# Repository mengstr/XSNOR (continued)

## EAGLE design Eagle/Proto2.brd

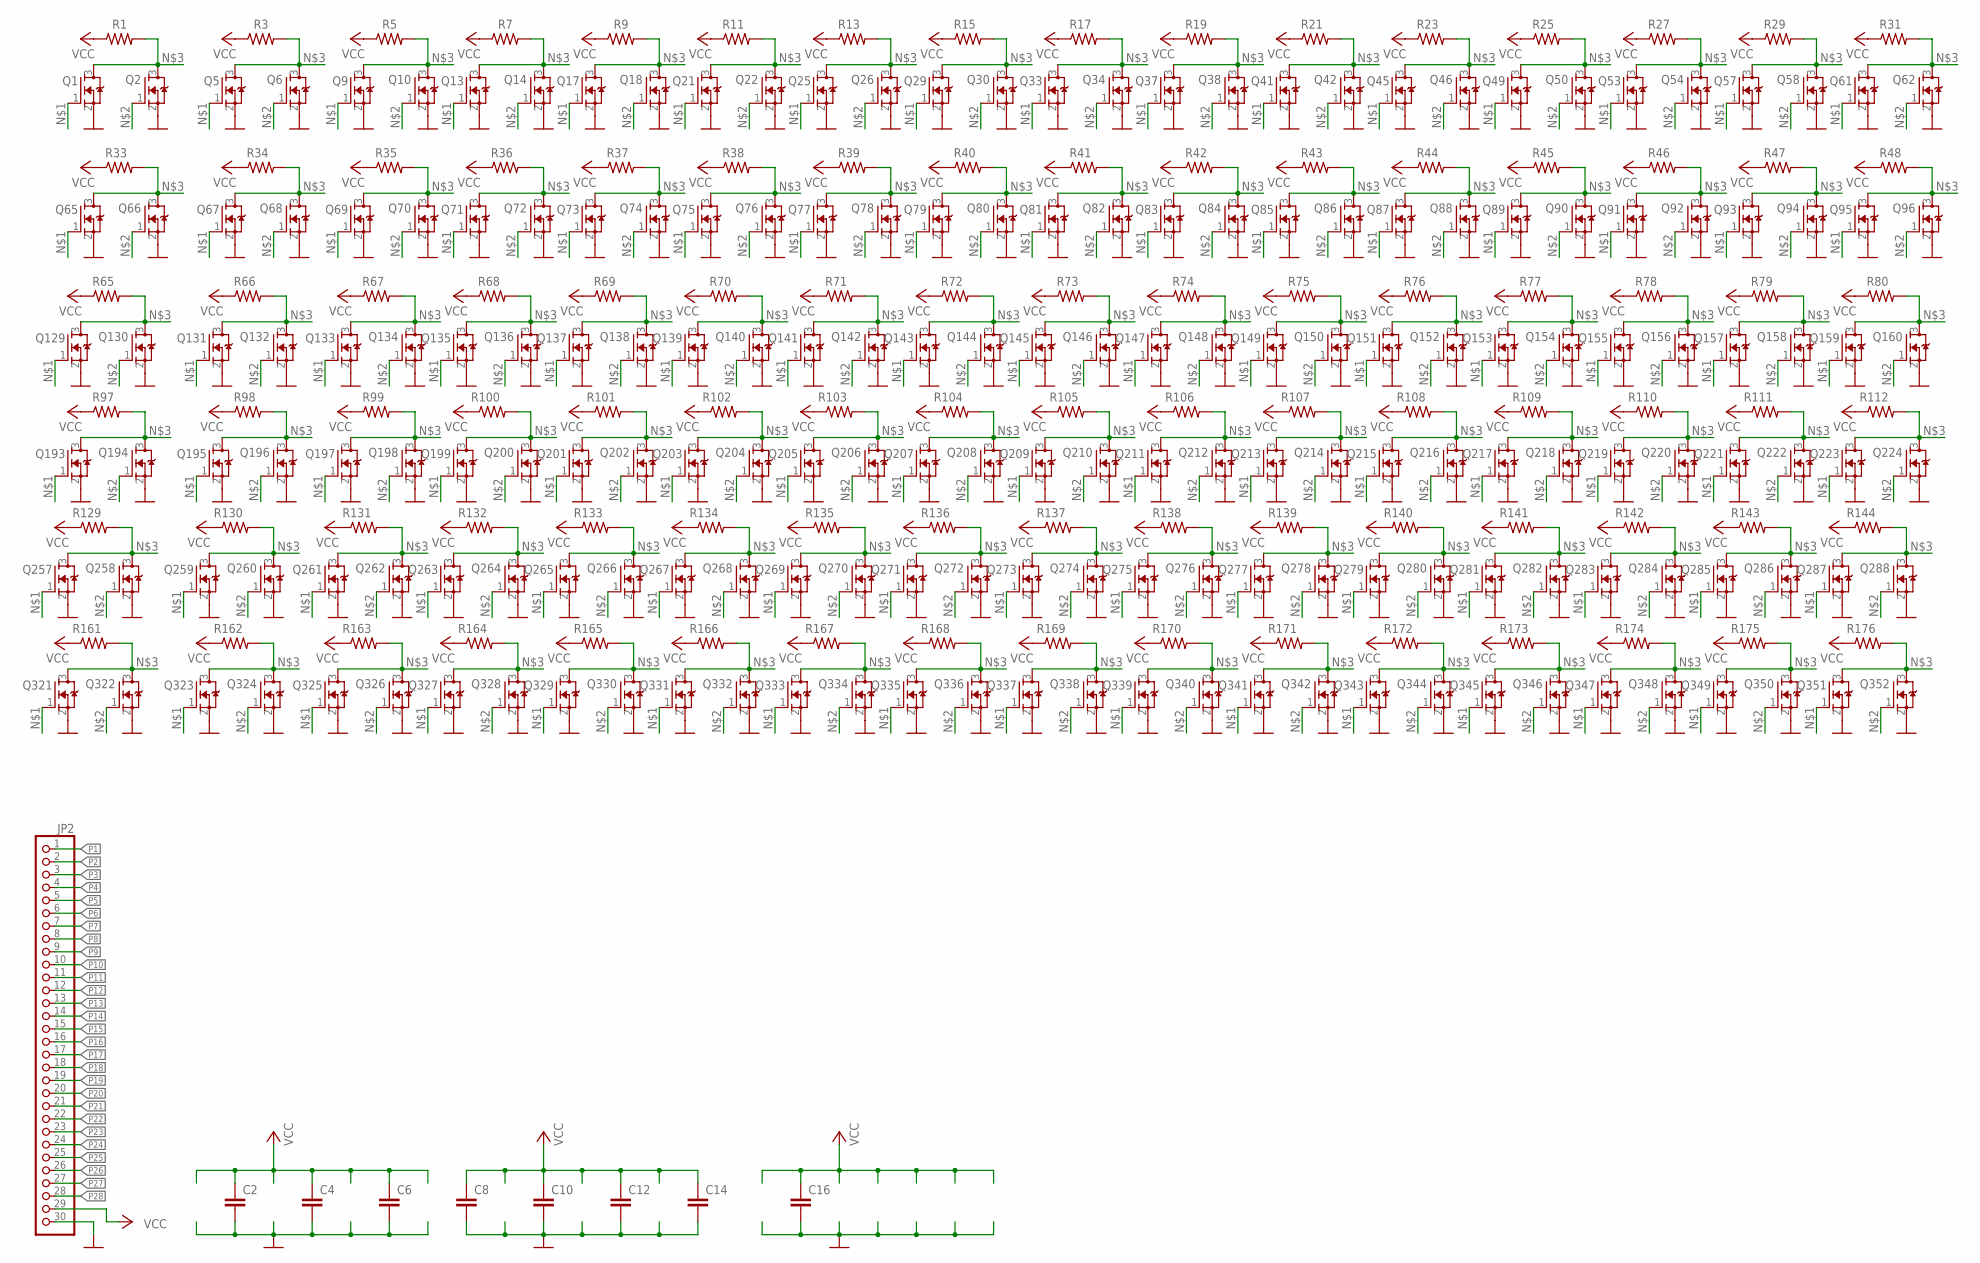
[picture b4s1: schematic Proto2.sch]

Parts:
C2, C4, C6, C8, C10, C12, C14, C16: C-EUC0805K; C0805K
JP2: PINHD-1X30; 1X30
Q1, Q2, Q5, Q6, Q9, Q10, Q13, Q14, Q17, Q18, Q21, Q22, Q25, Q26, Q29, Q30, Q33, Q34, Q37, Q38, Q41, Q42, Q45, Q46, Q49, Q50, Q53, Q54, Q57, Q58, Q61, Q62, Q65, Q66, Q67, Q68, Q69, Q70, Q71, Q72, Q73, Q74, Q75, Q76, Q77, Q78, Q79, Q80, Q81, Q82, Q83, Q84, Q85, Q86, Q87, Q88, Q89, Q90, Q91, Q92, Q93, Q94, Q95, Q96, Q129, Q130, Q131, Q132, Q133, Q134, Q135, Q136, Q137, Q138, Q139, Q140, Q141, Q142, Q143, Q144, Q145, Q146, Q147, Q148, Q149, Q150, Q151, Q152, Q153, Q154, Q155, Q156, Q157, Q158, Q159, Q160, Q193, Q194, Q195, Q196, Q197, Q198, Q199, Q200, Q201, Q202, Q203, Q204, Q205, Q206, Q207, Q208, Q209, Q210, Q211, Q212, Q213, Q214, Q215, Q216, Q217, Q218, Q219, Q220, Q221, Q222, Q223, Q224, Q257, Q258, Q259, Q260, Q261, Q262, Q263, Q264, Q265, Q266, Q267, Q268, Q269, Q270, Q271, Q272, Q273, Q274, Q275, Q276, Q277, Q278, Q279, Q280, Q281, Q282, Q283, Q284, Q285, Q286, Q287, Q288, Q321, Q322, Q323, Q324, Q325, Q326, Q327, Q328, Q329, Q330, Q331, Q332, Q333, Q334, Q335, Q336, Q337, Q338, Q339, Q340, Q341, Q342, Q343, Q344, Q345, Q346, Q347, Q348, Q349, Q350, Q351, Q352: 310mA/60V/1.6Ω; SOT23
R1, R3, R5, R7, R9, R11, R13, R15, R17, R19, R21, R23, R25, R27, R29, R31, R33, R34, R35, R36, R37, R38, R39, R40, R41, R42, R43, R44, R45, R46, R47, R48, R65, R66, R67, R68, R69, R70, R71, R72, R73, R74, R75, R76, R77, R78, R79, R80, R97, R98, R99, R100, R101, R102, R103, R104, R105, R106, R107, R108, R109, R110, R111, R112, R129, R130, R131, R132, R133, R134, R135, R136, R137, R138, R139, R140, R141, R142, R143, R144, R161, R162, R163, R164, R165, R166, R167, R168, R169, R170, R171, R172, R173, R174, R175, R176: 0805

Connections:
GND: C2.2, C4.2, C6.2, C8.2, C10.2, C12.2, C14.2, C16.2, JP2.30, Q1.2 (S), Q2.2 (S), Q5.2 (S), Q6.2 (S), Q9.2 (S), Q10.2 (S), Q13.2 (S), Q14.2 (S), Q17.2 (S), Q18.2 (S), Q21.2 (S), Q22.2 (S), Q25.2 (S), Q26.2 (S), Q29.2 (S), Q30.2 (S), Q33.2 (S), Q34.2 (S), Q37.2 (S), Q38.2 (S), Q41.2 (S), Q42.2 (S), Q45.2 (S), Q46.2 (S), Q49.2 (S), Q50.2 (S), Q53.2 (S), Q54.2 (S), Q57.2 (S), Q58.2 (S), Q61.2 (S), Q62.2 (S), Q65.2 (S), Q66.2 (S), Q67.2 (S), Q68.2 (S), Q69.2 (S), Q70.2 (S), Q71.2 (S), Q72.2 (S), Q73.2 (S), Q74.2 (S), Q75.2 (S), Q76.2 (S), Q77.2 (S), Q78.2 (S), Q79.2 (S), Q80.2 (S), Q81.2 (S), Q82.2 (S), Q83.2 (S), Q84.2 (S), Q85.2 (S), Q86.2 (S), Q87.2 (S), Q88.2 (S), Q89.2 (S), Q90.2 (S), Q91.2 (S), Q92.2 (S), Q93.2 (S), Q94.2 (S), Q95.2 (S), Q96.2 (S), Q129.2 (S), Q130.2 (S), Q131.2 (S), Q132.2 (S), Q133.2 (S), Q134.2 (S), Q135.2 (S), Q136.2 (S), Q137.2 (S), Q138.2 (S), Q139.2 (S), Q140.2 (S), Q141.2 (S), Q142.2 (S), Q143.2 (S), Q144.2 (S), Q145.2 (S), Q146.2 (S), Q147.2 (S), Q148.2 (S), Q149.2 (S), Q150.2 (S), Q151.2 (S), Q152.2 (S), Q153.2 (S), Q154.2 (S), Q155.2 (S), Q156.2 (S), Q157.2 (S), Q158.2 (S), Q159.2 (S), Q160.2 (S), Q193.2 (S), Q194.2 (S), Q195.2 (S), Q196.2 (S), Q197.2 (S), Q198.2 (S), Q199.2 (S), Q200.2 (S), Q201.2 (S), Q202.2 (S), Q203.2 (S), Q204.2 (S), Q205.2 (S), Q206.2 (S), Q207.2 (S), Q208.2 (S), Q209.2 (S), Q210.2 (S), Q211.2 (S), Q212.2 (S), Q213.2 (S), Q214.2 (S), Q215.2 (S), Q216.2 (S), Q217.2 (S), Q218.2 (S), Q219.2 (S), Q220.2 (S), Q221.2 (S), Q222.2 (S), Q223.2 (S), Q224.2 (S), Q257.2 (S), Q258.2 (S), Q259.2 (S), Q260.2 (S), Q261.2 (S), Q262.2 (S), Q263.2 (S), Q264.2 (S), Q265.2 (S), Q266.2 (S), Q267.2 (S), Q268.2 (S), Q269.2 (S), Q270.2 (S), Q271.2 (S), Q272.2 (S), Q273.2 (S), Q274.2 (S), Q275.2 (S), Q276.2 (S), Q277.2 (S), Q278.2 (S), Q279.2 (S), Q280.2 (S), Q281.2 (S), Q282.2 (S), Q283.2 (S), Q284.2 (S), Q285.2 (S), Q286.2 (S), Q287.2 (S), Q288.2 (S), Q321.2 (S), Q322.2 (S), Q323.2 (S), Q324.2 (S), Q325.2 (S), Q326.2 (S), Q327.2 (S), Q328.2 (S), Q329.2 (S), Q330.2 (S), Q331.2 (S), Q332.2 (S), Q333.2 (S), Q334.2 (S), Q335.2 (S), Q336.2 (S), Q337.2 (S), Q338.2 (S), Q339.2 (S), Q340.2 (S), Q341.2 (S), Q342.2 (S), Q343.2 (S), Q344.2 (S), Q345.2 (S), Q346.2 (S), Q347.2 (S), Q348.2 (S), Q349.2 (S), Q350.2 (S), Q351.2 (S), Q352.2 (S)
unnamed: Q1.1 (G), Q5.1 (G), Q9.1 (G), Q13.1 (G), Q17.1 (G), Q21.1 (G), Q25.1 (G), Q29.1 (G), Q33.1 (G), Q37.1 (G), Q41.1 (G), Q45.1 (G), Q49.1 (G), Q53.1 (G), Q57.1 (G), Q61.1 (G), Q65.1 (G), Q67.1 (G), Q69.1 (G), Q71.1 (G), Q73.1 (G), Q75.1 (G), Q77.1 (G), Q79.1 (G), Q81.1 (G), Q83.1 (G), Q85.1 (G), Q87.1 (G), Q89.1 (G), Q91.1 (G), Q93.1 (G), Q95.1 (G), Q129.1 (G), Q131.1 (G), Q133.1 (G), Q135.1 (G), Q137.1 (G), Q139.1 (G), Q141.1 (G), Q143.1 (G), Q145.1 (G), Q147.1 (G), Q149.1 (G), Q151.1 (G), Q153.1 (G), Q155.1 (G), Q157.1 (G), Q159.1 (G), Q193.1 (G), Q195.1 (G), Q197.1 (G), Q199.1 (G), Q201.1 (G), Q203.1 (G), Q205.1 (G), Q207.1 (G), Q209.1 (G), Q211.1 (G), Q213.1 (G), Q215.1 (G), Q217.1 (G), Q219.1 (G), Q221.1 (G), Q223.1 (G), Q257.1 (G), Q259.1 (G), Q261.1 (G), Q263.1 (G), Q265.1 (G), Q267.1 (G), Q269.1 (G), Q271.1 (G), Q273.1 (G), Q275.1 (G), Q277.1 (G), Q279.1 (G), Q281.1 (G), Q283.1 (G), Q285.1 (G), Q287.1 (G), Q321.1 (G), Q323.1 (G), Q325.1 (G), Q327.1 (G), Q329.1 (G), Q331.1 (G), Q333.1 (G), Q335.1 (G), Q337.1 (G), Q339.1 (G), Q341.1 (G), Q343.1 (G), Q345.1 (G), Q347.1 (G), Q349.1 (G), Q351.1 (G)
unnamed: Q2.1 (G), Q6.1 (G), Q10.1 (G), Q14.1 (G), Q18.1 (G), Q22.1 (G), Q26.1 (G), Q30.1 (G), Q34.1 (G), Q38.1 (G), Q42.1 (G), Q46.1 (G), Q50.1 (G), Q54.1 (G), Q58.1 (G), Q62.1 (G), Q66.1 (G), Q68.1 (G), Q70.1 (G), Q72.1 (G), Q74.1 (G), Q76.1 (G), Q78.1 (G), Q80.1 (G), Q82.1 (G), Q84.1 (G), Q86.1 (G), Q88.1 (G), Q90.1 (G), Q92.1 (G), Q94.1 (G), Q96.1 (G), Q130.1 (G), Q132.1 (G), Q134.1 (G), Q136.1 (G), Q138.1 (G), Q140.1 (G), Q142.1 (G), Q144.1 (G), Q146.1 (G), Q148.1 (G), Q150.1 (G), Q152.1 (G), Q154.1 (G), Q156.1 (G), Q158.1 (G), Q160.1 (G), Q194.1 (G), Q196.1 (G), Q198.1 (G), Q200.1 (G), Q202.1 (G), Q204.1 (G), Q206.1 (G), Q208.1 (G), Q210.1 (G), Q212.1 (G), Q214.1 (G), Q216.1 (G), Q218.1 (G), Q220.1 (G), Q222.1 (G), Q224.1 (G), Q258.1 (G), Q260.1 (G), Q262.1 (G), Q264.1 (G), Q266.1 (G), Q268.1 (G), Q270.1 (G), Q272.1 (G), Q274.1 (G), Q276.1 (G), Q278.1 (G), Q280.1 (G), Q282.1 (G), Q284.1 (G), Q286.1 (G), Q288.1 (G), Q322.1 (G), Q324.1 (G), Q326.1 (G), Q328.1 (G), Q330.1 (G), Q332.1 (G), Q334.1 (G), Q336.1 (G), Q338.1 (G), Q340.1 (G), Q342.1 (G), Q344.1 (G), Q346.1 (G), Q348.1 (G), Q350.1 (G), Q352.1 (G)
unnamed: Q1.3 (D), Q2.3 (D), Q5.3 (D), Q6.3 (D), Q9.3 (D), Q10.3 (D), Q13.3 (D), Q14.3 (D), Q17.3 (D), Q18.3 (D), Q21.3 (D), Q22.3 (D), Q25.3 (D), Q26.3 (D), Q29.3 (D), Q30.3 (D), Q33.3 (D), Q34.3 (D), Q37.3 (D), Q38.3 (D), Q41.3 (D), Q42.3 (D), Q45.3 (D), Q46.3 (D), Q49.3 (D), Q50.3 (D), Q53.3 (D), Q54.3 (D), Q57.3 (D), Q58.3 (D), Q61.3 (D), Q62.3 (D), Q65.3 (D), Q66.3 (D), Q67.3 (D), Q68.3 (D), Q69.3 (D), Q70.3 (D), Q71.3 (D), Q72.3 (D), Q73.3 (D), Q74.3 (D), Q75.3 (D), Q76.3 (D), Q77.3 (D), Q78.3 (D), Q79.3 (D), Q80.3 (D), Q81.3 (D), Q82.3 (D), Q83.3 (D), Q84.3 (D), Q85.3 (D), Q86.3 (D), Q87.3 (D), Q88.3 (D), Q89.3 (D), Q90.3 (D), Q91.3 (D), Q92.3 (D), Q93.3 (D), Q94.3 (D), Q95.3 (D), Q96.3 (D), Q129.3 (D), Q130.3 (D), Q131.3 (D), Q132.3 (D), Q133.3 (D), Q134.3 (D), Q135.3 (D), Q136.3 (D), Q137.3 (D), Q138.3 (D), Q139.3 (D), Q140.3 (D), Q141.3 (D), Q142.3 (D), Q143.3 (D), Q144.3 (D), Q145.3 (D), Q146.3 (D), Q147.3 (D), Q148.3 (D), Q149.3 (D), Q150.3 (D), Q151.3 (D), Q152.3 (D), Q153.3 (D), Q154.3 (D), Q155.3 (D), Q156.3 (D), Q157.3 (D), Q158.3 (D), Q159.3 (D), Q160.3 (D), Q193.3 (D), Q194.3 (D), Q195.3 (D), Q196.3 (D), Q197.3 (D), Q198.3 (D), Q199.3 (D), Q200.3 (D), Q201.3 (D), Q202.3 (D), Q203.3 (D), Q204.3 (D), Q205.3 (D), Q206.3 (D), Q207.3 (D), Q208.3 (D), Q209.3 (D), Q210.3 (D), Q211.3 (D), Q212.3 (D), Q213.3 (D), Q214.3 (D), Q215.3 (D), Q216.3 (D), Q217.3 (D), Q218.3 (D), Q219.3 (D), Q220.3 (D), Q221.3 (D), Q222.3 (D), Q223.3 (D), Q224.3 (D), Q257.3 (D), Q258.3 (D), Q259.3 (D), Q260.3 (D), Q261.3 (D), Q262.3 (D), Q263.3 (D), Q264.3 (D), Q265.3 (D), Q266.3 (D), Q267.3 (D), Q268.3 (D), Q269.3 (D), Q270.3 (D), Q271.3 (D), Q272.3 (D), Q273.3 (D), Q274.3 (D), Q275.3 (D), Q276.3 (D), Q277.3 (D), Q278.3 (D), Q279.3 (D), Q280.3 (D), Q281.3 (D), Q282.3 (D), Q283.3 (D), Q284.3 (D), Q285.3 (D), Q286.3 (D), Q287.3 (D), Q288.3 (D), Q321.3 (D), Q322.3 (D), Q323.3 (D), Q324.3 (D), Q325.3 (D), Q326.3 (D), Q327.3 (D), Q328.3 (D), Q329.3 (D), Q330.3 (D), Q331.3 (D), Q332.3 (D), Q333.3 (D), Q334.3 (D), Q335.3 (D), Q336.3 (D), Q337.3 (D), Q338.3 (D), Q339.3 (D), Q340.3 (D), Q341.3 (D), Q342.3 (D), Q343.3 (D), Q344.3 (D), Q345.3 (D), Q346.3 (D), Q347.3 (D), Q348.3 (D), Q349.3 (D), Q350.3 (D), Q351.3 (D), Q352.3 (D), R1.2, R3.2, R5.2, R7.2, R9.2, R11.2, R13.2, R15.2, R17.2, R19.2, R21.2, R23.2, R25.2, R27.2, R29.2, R31.2, R33.2, R34.2, R35.2, R36.2, R37.2, R38.2, R39.2, R40.2, R41.2, R42.2, R43.2, R44.2, R45.2, R46.2, R47.2, R48.2, R65.2, R66.2, R67.2, R68.2, R69.2, R70.2, R71.2, R72.2, R73.2, R74.2, R75.2, R76.2, R77.2, R78.2, R79.2, R80.2, R97.2, R98.2, R99.2, R100.2, R101.2, R102.2, R103.2, R104.2, R105.2, R106.2, R107.2, R108.2, R109.2, R110.2, R111.2, R112.2, R129.2, R130.2, R131.2, R132.2, R133.2, R134.2, R135.2, R136.2, R137.2, R138.2, R139.2, R140.2, R141.2, R142.2, R143.2, R144.2, R161.2, R162.2, R163.2, R164.2, R165.2, R166.2, R167.2, R168.2, R169.2, R170.2, R171.2, R172.2, R173.2, R174.2, R175.2, R176.2
P1: JP2.1
P2: JP2.2
P3: JP2.3
P4: JP2.4
P5: JP2.5
P6: JP2.6
P7: JP2.7
P8: JP2.8
P9: JP2.9
P10: JP2.10
P11: JP2.11
P12: JP2.12
P13: JP2.13
P14: JP2.14
P15: JP2.15
P16: JP2.16
P17: JP2.17
P18: JP2.18
P19: JP2.19
P20: JP2.20
P21: JP2.21
P22: JP2.22
P23: JP2.23
P24: JP2.24
P25: JP2.25
P26: JP2.26
P27: JP2.27
P28: JP2.28
VCC: C2.1, C4.1, C6.1, C8.1, C10.1, C12.1, C14.1, C16.1, JP2.29, R1.1, R3.1, R5.1, R7.1, R9.1, R11.1, R13.1, R15.1, R17.1, R19.1, R21.1, R23.1, R25.1, R27.1, R29.1, R31.1, R33.1, R34.1, R35.1, R36.1, R37.1, R38.1, R39.1, R40.1, R41.1, R42.1, R43.1, R44.1, R45.1, R46.1, R47.1, R48.1, R65.1, R66.1, R67.1, R68.1, R69.1, R70.1, R71.1, R72.1, R73.1, R74.1, R75.1, R76.1, R77.1, R78.1, R79.1, R80.1, R97.1, R98.1, R99.1, R100.1, R101.1, R102.1, R103.1, R104.1, R105.1, R106.1, R107.1, R108.1, R109.1, R110.1, R111.1, R112.1, R129.1, R130.1, R131.1, R132.1, R133.1, R134.1, R135.1, R136.1, R137.1, R138.1, R139.1, R140.1, R141.1, R142.1, R143.1, R144.1, R161.1, R162.1, R163.1, R164.1, R165.1, R166.1, R167.1, R168.1, R169.1, R170.1, R171.1, R172.1, R173.1, R174.1, R175.1, R176.1

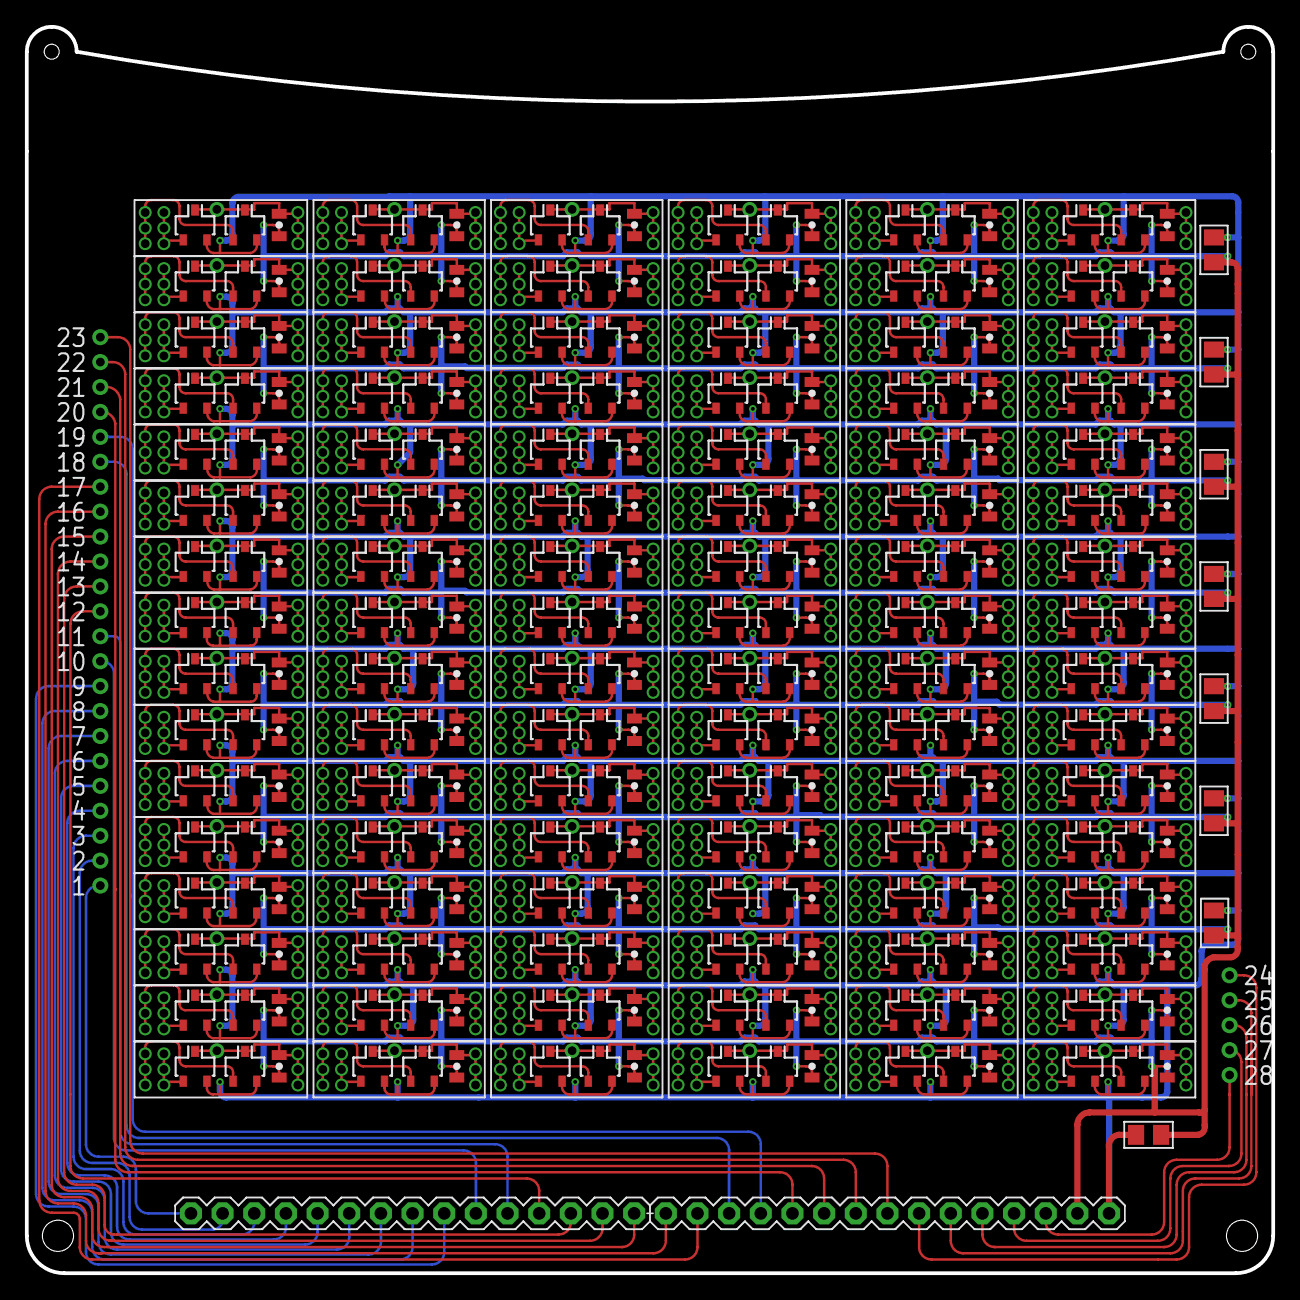
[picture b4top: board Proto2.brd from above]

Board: 2 copper layers, 100.0 x 100.0 mm, 297 parts (0 on the bottom side), 5 nets.

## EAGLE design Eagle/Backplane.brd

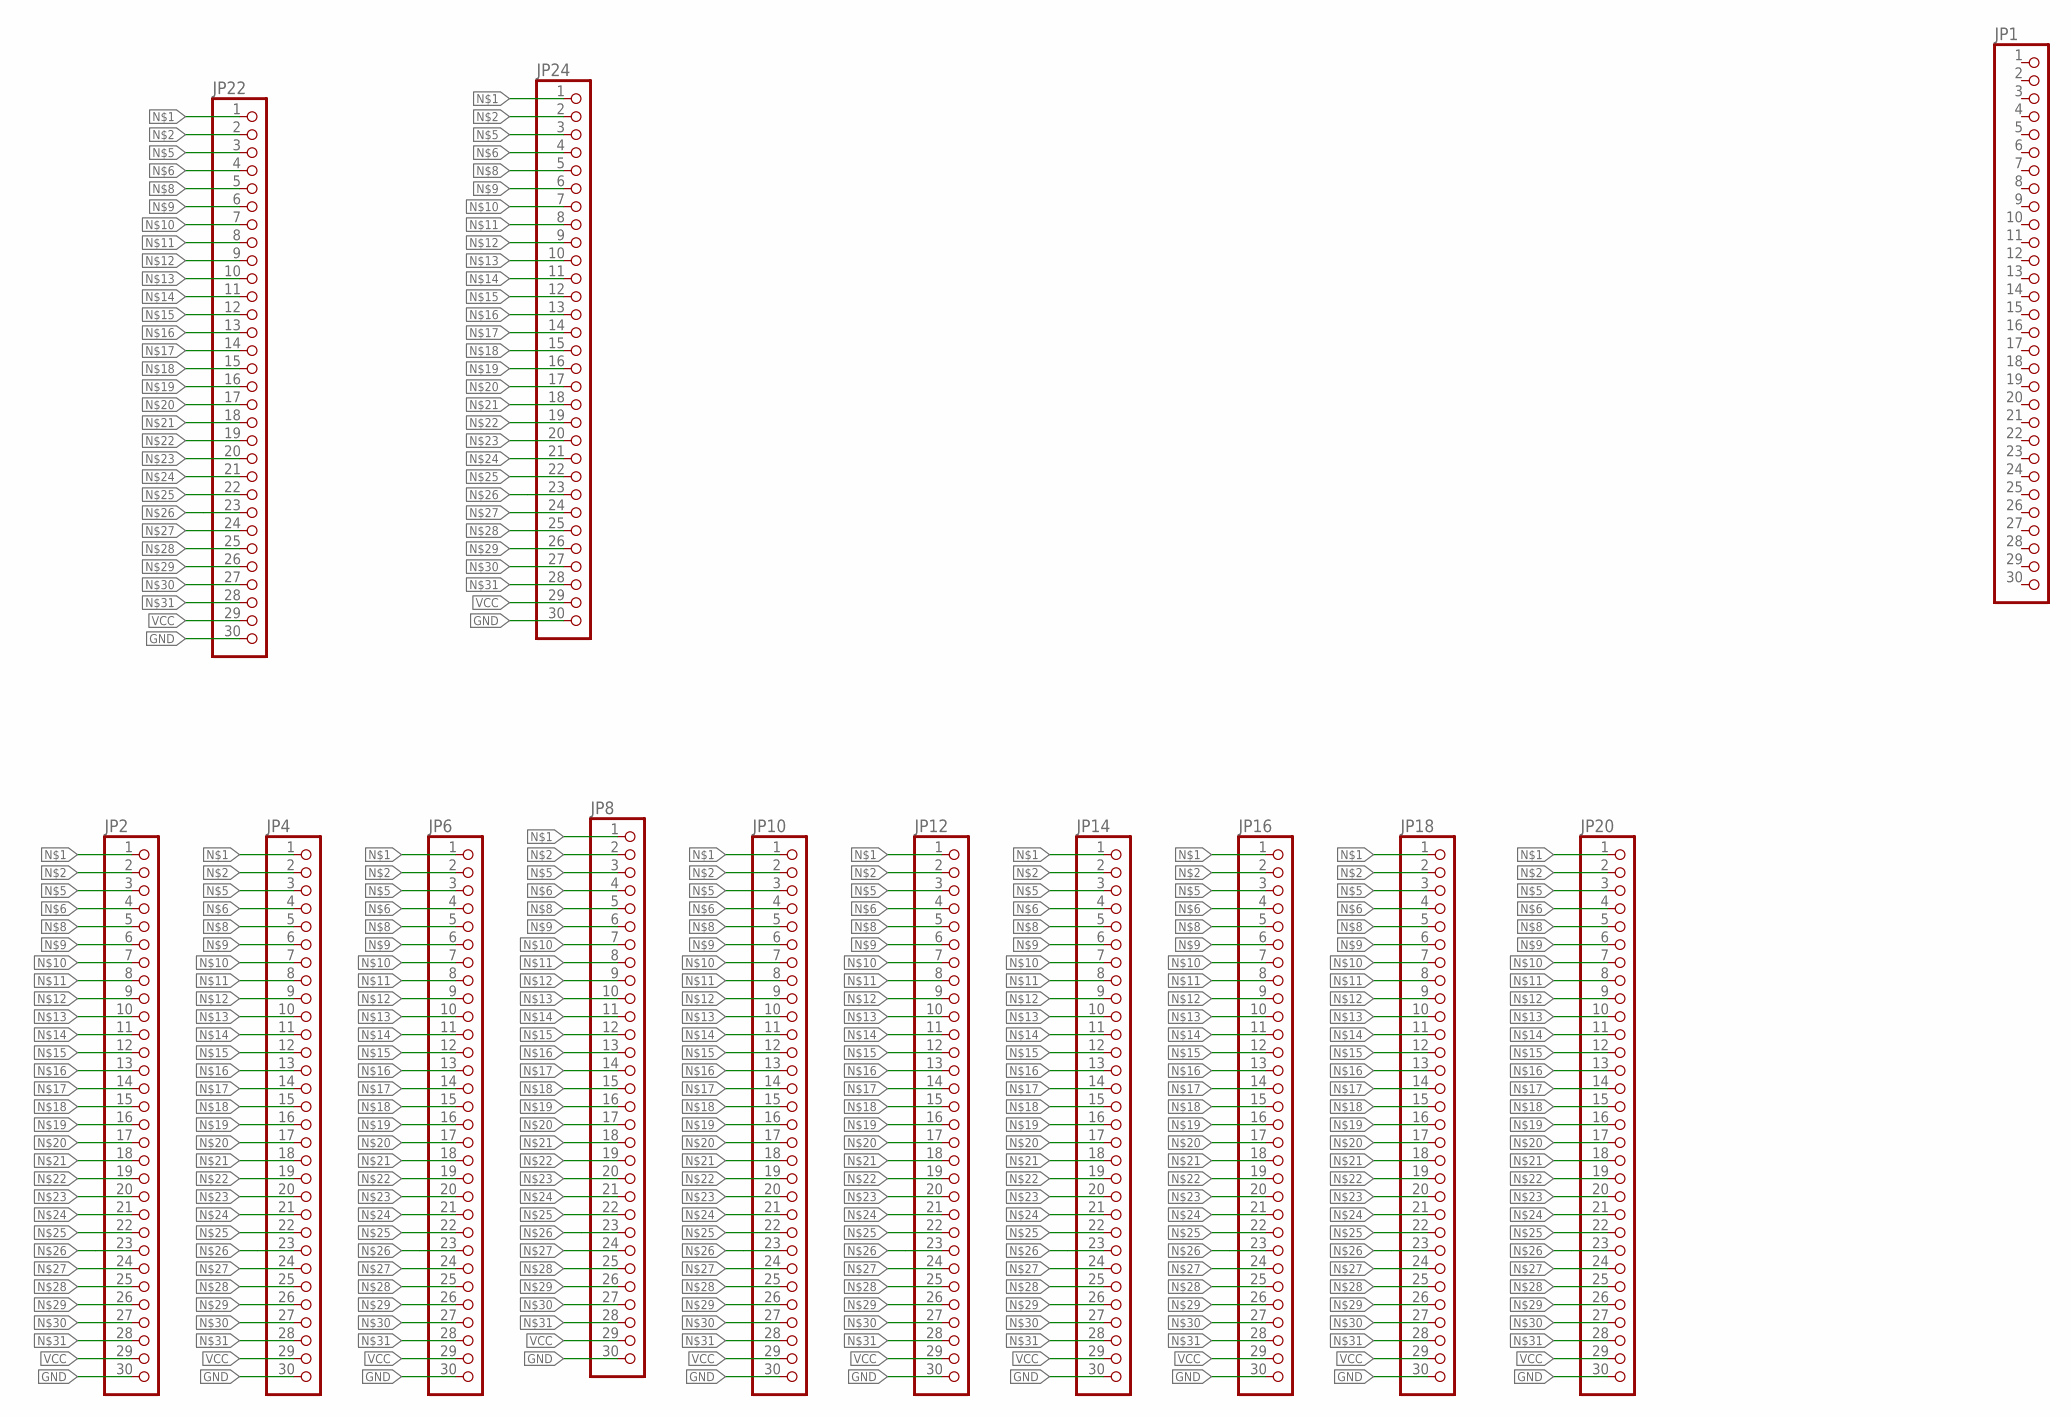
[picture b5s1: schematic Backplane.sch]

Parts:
JP1, JP2, JP4, JP6, JP8, JP10, JP12, JP14, JP16, JP18, JP20, JP22, JP24: PINHD-1X30; 1X30

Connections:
GND: JP2.30, JP4.30, JP6.30, JP8.30, JP10.30, JP12.30, JP14.30, JP16.30, JP18.30, JP20.30, JP22.30, JP24.30
unnamed: JP2.1, JP4.1, JP6.1, JP8.1, JP10.1, JP12.1, JP14.1, JP16.1, JP18.1, JP20.1, JP22.1, JP24.1
unnamed: JP2.2, JP4.2, JP6.2, JP8.2, JP10.2, JP12.2, JP14.2, JP16.2, JP18.2, JP20.2, JP22.2, JP24.2
unnamed: JP2.3, JP4.3, JP6.3, JP8.3, JP10.3, JP12.3, JP14.3, JP16.3, JP18.3, JP20.3, JP22.3, JP24.3
unnamed: JP2.4, JP4.4, JP6.4, JP8.4, JP10.4, JP12.4, JP14.4, JP16.4, JP18.4, JP20.4, JP22.4, JP24.4
unnamed: JP2.5, JP4.5, JP6.5, JP8.5, JP10.5, JP12.5, JP14.5, JP16.5, JP18.5, JP20.5, JP22.5, JP24.5
unnamed: JP2.6, JP4.6, JP6.6, JP8.6, JP10.6, JP12.6, JP14.6, JP16.6, JP18.6, JP20.6, JP22.6, JP24.6
unnamed: JP2.7, JP4.7, JP6.7, JP8.7, JP10.7, JP12.7, JP14.7, JP16.7, JP18.7, JP20.7, JP22.7, JP24.7
unnamed: JP2.8, JP4.8, JP6.8, JP8.8, JP10.8, JP12.8, JP14.8, JP16.8, JP18.8, JP20.8, JP22.8, JP24.8
unnamed: JP2.9, JP4.9, JP6.9, JP8.9, JP10.9, JP12.9, JP14.9, JP16.9, JP18.9, JP20.9, JP22.9, JP24.9
unnamed: JP2.10, JP4.10, JP6.10, JP8.10, JP10.10, JP12.10, JP14.10, JP16.10, JP18.10, JP20.10, JP22.10, JP24.10
unnamed: JP2.11, JP4.11, JP6.11, JP8.11, JP10.11, JP12.11, JP14.11, JP16.11, JP18.11, JP20.11, JP22.11, JP24.11
unnamed: JP2.12, JP4.12, JP6.12, JP8.12, JP10.12, JP12.12, JP14.12, JP16.12, JP18.12, JP20.12, JP22.12, JP24.12
unnamed: JP2.13, JP4.13, JP6.13, JP8.13, JP10.13, JP12.13, JP14.13, JP16.13, JP18.13, JP20.13, JP22.13, JP24.13
unnamed: JP2.14, JP4.14, JP6.14, JP8.14, JP10.14, JP12.14, JP14.14, JP16.14, JP18.14, JP20.14, JP22.14, JP24.14
unnamed: JP2.15, JP4.15, JP6.15, JP8.15, JP10.15, JP12.15, JP14.15, JP16.15, JP18.15, JP20.15, JP22.15, JP24.15
unnamed: JP2.16, JP4.16, JP6.16, JP8.16, JP10.16, JP12.16, JP14.16, JP16.16, JP18.16, JP20.16, JP22.16, JP24.16
unnamed: JP2.17, JP4.17, JP6.17, JP8.17, JP10.17, JP12.17, JP14.17, JP16.17, JP18.17, JP20.17, JP22.17, JP24.17
unnamed: JP2.18, JP4.18, JP6.18, JP8.18, JP10.18, JP12.18, JP14.18, JP16.18, JP18.18, JP20.18, JP22.18, JP24.18
unnamed: JP2.19, JP4.19, JP6.19, JP8.19, JP10.19, JP12.19, JP14.19, JP16.19, JP18.19, JP20.19, JP22.19, JP24.19
unnamed: JP2.20, JP4.20, JP6.20, JP8.20, JP10.20, JP12.20, JP14.20, JP16.20, JP18.20, JP20.20, JP22.20, JP24.20
unnamed: JP2.21, JP4.21, JP6.21, JP8.21, JP10.21, JP12.21, JP14.21, JP16.21, JP18.21, JP20.21, JP22.21, JP24.21
unnamed: JP2.22, JP4.22, JP6.22, JP8.22, JP10.22, JP12.22, JP14.22, JP16.22, JP18.22, JP20.22, JP22.22, JP24.22
unnamed: JP2.23, JP4.23, JP6.23, JP8.23, JP10.23, JP12.23, JP14.23, JP16.23, JP18.23, JP20.23, JP22.23, JP24.23
unnamed: JP2.24, JP4.24, JP6.24, JP8.24, JP10.24, JP12.24, JP14.24, JP16.24, JP18.24, JP20.24, JP22.24, JP24.24
unnamed: JP2.25, JP4.25, JP6.25, JP8.25, JP10.25, JP12.25, JP14.25, JP16.25, JP18.25, JP20.25, JP22.25, JP24.25
unnamed: JP2.26, JP4.26, JP6.26, JP8.26, JP10.26, JP12.26, JP14.26, JP16.26, JP18.26, JP20.26, JP22.26, JP24.26
unnamed: JP2.27, JP4.27, JP6.27, JP8.27, JP10.27, JP12.27, JP14.27, JP16.27, JP18.27, JP20.27, JP22.27, JP24.27
unnamed: JP2.28, JP4.28, JP6.28, JP8.28, JP10.28, JP12.28, JP14.28, JP16.28, JP18.28, JP20.28, JP22.28, JP24.28
VCC: JP2.29, JP4.29, JP6.29, JP8.29, JP10.29, JP12.29, JP14.29, JP16.29, JP18.29, JP20.29, JP22.29, JP24.29

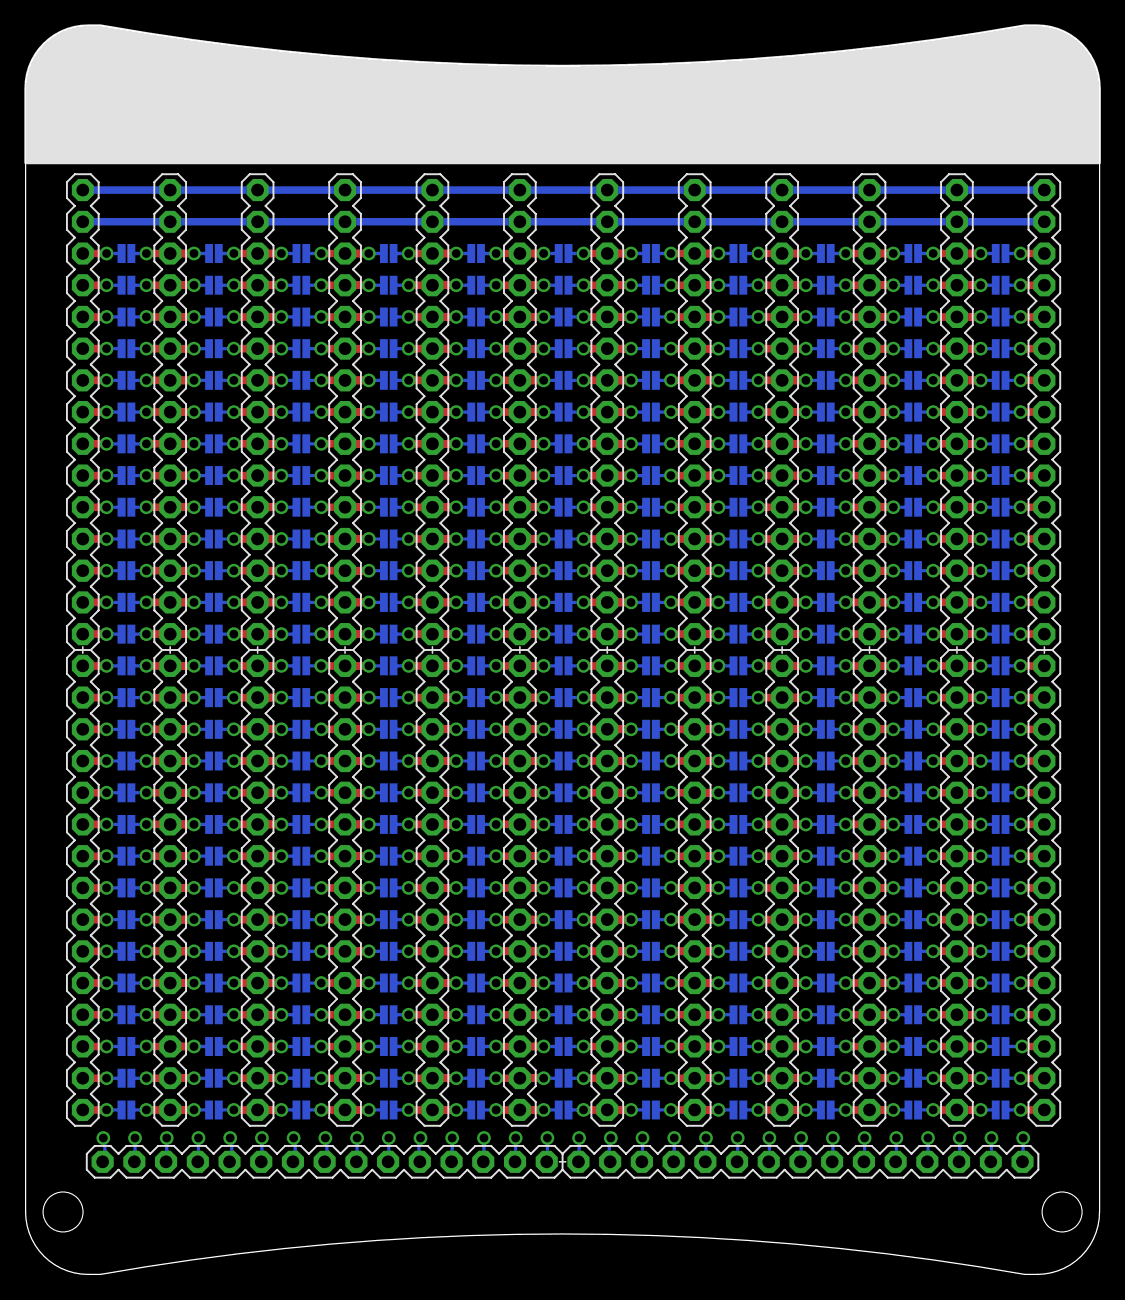
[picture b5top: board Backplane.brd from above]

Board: 2 copper layers, 86.0 x 100.0 mm, 13 parts (0 on the bottom side), 30 nets.

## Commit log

2017-12-26 Rerouted for SOT23
2017-12-26 Doc for pinout of PCB's
2017-12-26 Ignore backups of design blocks
2017-12-26 Copy of Eagel Design blocks
2017-12-26 Centered design on PCB
2017-12-28 Add NOR2 Proto board
2017-12-28 Cleanups of PCBs
2017-12-28 Spice files for Keyboard
2017-12-29 Keyboard decoder pcb
2017-12-30 Silk cleanup. Routing of GND instead of floodfill
2017-12-30 Add Keyboard Decoder pinout
2017-12-30 Removed double label
2018-01-03 PCB template
2018-01-03 Common generic backplane
2018-01-03 Updated boards with pcb template
2018-01-03 Minor cleanup of board
2018-01-03 12 step Johnsson counter (not finished)
2018-01-04 Finished Jonsson counter pcb
2018-01-04 Cleanup
2018-01-04 Logic simulation of Johnson counter
2018-01-04 Eagle test of Johnson counter
2018-01-04 Added component count on layer 49
2018-01-05 Updated with pcb template
2018-01-11 Added clear to ShiftReg
2018-01-12 Shiftreg pcb have its own inverters for control signals
